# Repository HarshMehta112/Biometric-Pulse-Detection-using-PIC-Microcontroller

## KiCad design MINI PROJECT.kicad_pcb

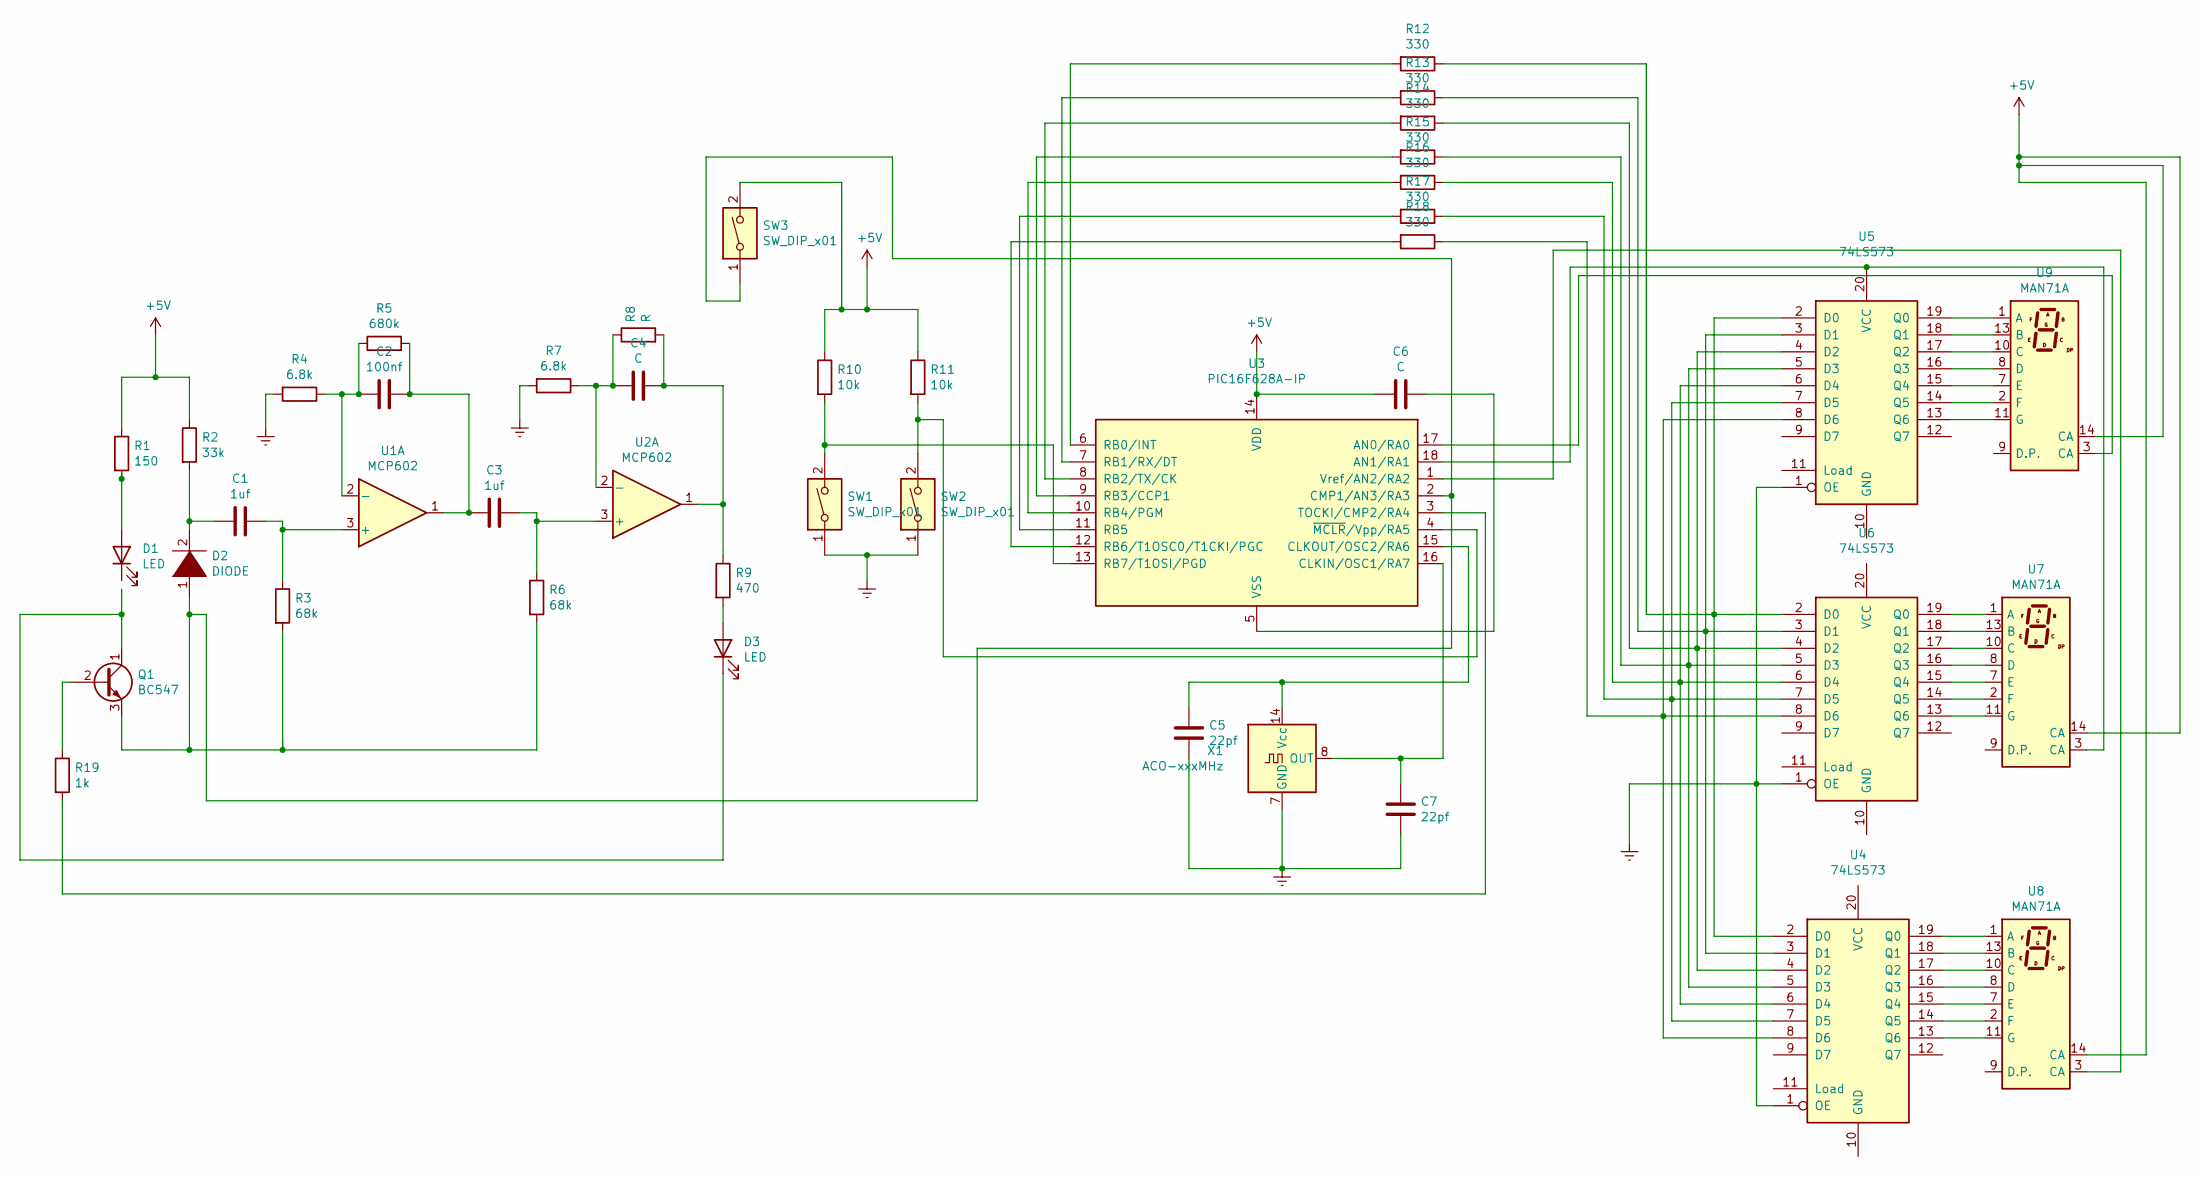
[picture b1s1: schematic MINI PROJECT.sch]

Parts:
C1, C3: 1uf; CP_Axial_L10.0mm_D4.5mm_P15.00mm_Horizontal
C2: 100nf; CP_Axial_L10.0mm_D4.5mm_P15.00mm_Horizontal
C4, C6: C; CP_Axial_L10.0mm_D4.5mm_P15.00mm_Horizontal
C5, C7: 22pf; CP_Axial_L10.0mm_D4.5mm_P15.00mm_Horizontal
D1, D3: LED; LED_D3.0mm_Horizontal_O1.27mm_Z2.0mm_IRBlack
D2: DIODE; D_5KPW_P7.62mm_Vertical_AnodeUp
Q1: BC547; TO-92_Inline
R1: 150; R_Axial_DIN0204_L3.6mm_D1.6mm_P1.90mm_Vertical
R2: 33k; R_Axial_DIN0204_L3.6mm_D1.6mm_P1.90mm_Vertical
R3, R6: 68k; R_Axial_DIN0204_L3.6mm_D1.6mm_P1.90mm_Vertical
R4, R7: 6.8k; R_Axial_DIN0204_L3.6mm_D1.6mm_P1.90mm_Vertical
R5: 680k; R_Axial_DIN0204_L3.6mm_D1.6mm_P1.90mm_Vertical
R8: R; R_Axial_DIN0204_L3.6mm_D1.6mm_P1.90mm_Vertical
R9: 470; R_Axial_DIN0204_L3.6mm_D1.6mm_P1.90mm_Vertical
R10, R11: 10k; R_Axial_DIN0204_L3.6mm_D1.6mm_P1.90mm_Vertical
R12, R13, R14, R15, R16, R17, R18: 330; R_Axial_DIN0204_L3.6mm_D1.6mm_P1.90mm_Vertical
R19: 1k; R_Axial_DIN0204_L3.6mm_D1.6mm_P1.90mm_Vertical
SW1, SW2, SW3: SW_DIP_x01; DIP-4_W7.62mm
U1: MCP602; Crystal_SMD_0603-4Pin_6.0x3.5mm
U2: MCP602; Crystal_SMD_0603-4Pin_6.0x3.5mm_HandSoldering
U3: PIC16F628A-IP; DIP254P762X533-18
U4, U5, U6: 74LS573; HSOP-20-1EP_11.0x15.9mm_P1.27mm_SlugDown
U7, U8, U9: MAN71A
X1: ACO-xxxMHz; Oscillator_DIP-14

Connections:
+5V: C6.2, R1.1, R2.1, R10.1, R11.1, SW3.2, U3.14 (VDD), U7.14 (CA), U8.14 (CA), U9.14 (CA)
Earth: C5.2, C7.2, R4.2, R7.2, SW1.1, SW2.1, U4.1 (OE), U5.1 (OE), U6.1 (OE), X1.7 (GND)
unnamed: C1.1, R3.1, U1.3 (+)
unnamed: C1.2, D2.2 (A), R2.2
unnamed: C2.1, C3.2, R5.2, U1.1
unnamed: C2.2, R4.1, R5.1, U1.2 (-)
unnamed: C3.1, R6.1, U2.3 (+)
unnamed: C4.1, R8.2, R9.1, U2.1
unnamed: C4.2, R7.1, R8.1, U2.2 (-)
unnamed: C5.1, U3.15 (CLKOUT/OSC2/RA6), X1.14 (Vcc)
unnamed: C6.1, U3.5 (VSS)
unnamed: C7.1, U3.16 (CLKIN/OSC1/RA7), X1.8 (OUT)
unnamed: D1.2 (A), R1.2
unnamed: D2.1 (K), Q1.3 (E), R3.2, R6.2, SW3.1, U3.2 (CMP1/AN3/RA3)
unnamed: D3.1 (K), Q1.1 (C)
unnamed: D3.2 (A), R9.2
unnamed: Q1.2 (B), R19.1
unnamed: R10.2, SW1.2, U3.13 (RB7/T1OSI/PGD)
unnamed: R11.2, SW2.2, U3.4 (~MCLR~/Vpp/RA5)
unnamed: R12.1, U4.2 (D0), U5.2 (D0), U6.2 (D0)
unnamed: R12.2, U3.6 (RB0/INT)
unnamed: R13.1, U4.3 (D1), U5.3 (D1), U6.3 (D1)
unnamed: R13.2, U3.7 (RB1/RX/DT)
unnamed: R14.1, U4.4 (D2), U5.4 (D2), U6.4 (D2)
unnamed: R14.2, U3.8 (RB2/TX/CK)
unnamed: R15.1, U4.5 (D3), U5.5 (D3), U6.5 (D3)
unnamed: R15.2, U3.9 (RB3/CCP1)
unnamed: R16.1, U4.6 (D4), U5.6 (D4), U6.6 (D4)
unnamed: R16.2, U3.10 (RB4/PGM)
unnamed: R17.1, U4.7 (D5), U5.7 (D5), U6.7 (D5)
unnamed: R17.2, U3.11 (RB5)
unnamed: R18.1, U4.8 (D6), U5.8 (D6), U6.8 (D6)
unnamed: R18.2, U3.12 (RB6/T1OSC0/T1CKI/PGC)
unnamed: R19.2, U3.3 (TOCKI/CMP2/RA4)
unnamed: U3.1 (Vref/AN2/RA2), U8.3 (CA)
unnamed: U3.17 (AN0/RA0), U9.3 (CA)
unnamed: U3.18 (AN1/RA1), U5.20 (VCC), U7.3 (CA)
unnamed: U4.13 (Q6), U8.11 (G)
unnamed: U4.14 (Q5), U8.2 (F)
unnamed: U4.15 (Q4), U8.7 (E)
unnamed: U4.16 (Q3), U8.8 (D)
unnamed: U4.17 (Q2), U8.10 (C)
unnamed: U4.18 (Q1), U8.13 (B)
unnamed: U4.19 (Q0), U8.1 (A)
unnamed: U5.13 (Q6), U9.11 (G)
unnamed: U5.14 (Q5), U9.2 (F)
unnamed: U5.15 (Q4), U9.7 (E)
unnamed: U5.16 (Q3), U9.8 (D)
unnamed: U5.17 (Q2), U9.10 (C)
unnamed: U5.18 (Q1), U9.13 (B)
unnamed: U5.19 (Q0), U9.1 (A)
unnamed: U6.13 (Q6), U7.11 (G)
unnamed: U6.14 (Q5), U7.2 (F)
unnamed: U6.15 (Q4), U7.7 (E)
unnamed: U6.16 (Q3), U7.8 (D)
unnamed: U6.17 (Q2), U7.10 (C)
unnamed: U6.18 (Q1), U7.13 (B)
unnamed: U6.19 (Q0), U7.1 (A)

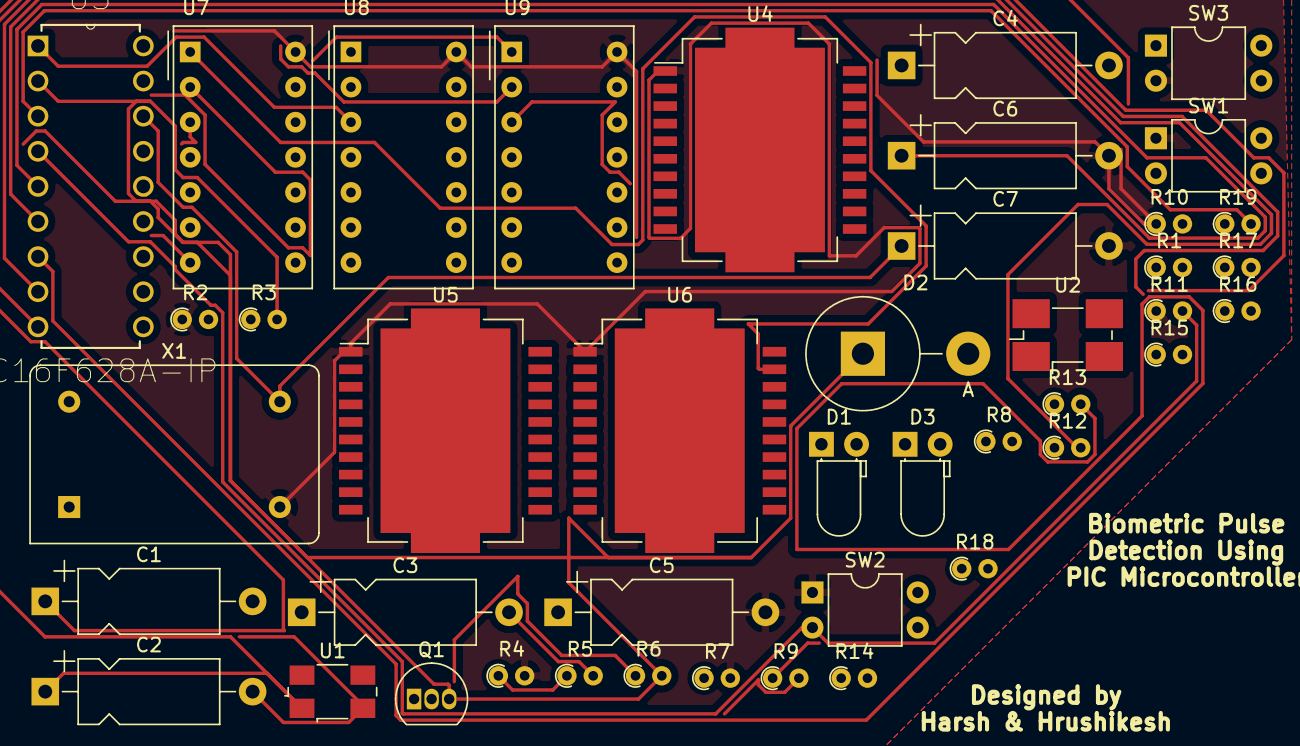
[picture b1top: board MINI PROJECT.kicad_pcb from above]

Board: 2 copper layers, 43 parts (0 on the bottom side), 58 nets.
